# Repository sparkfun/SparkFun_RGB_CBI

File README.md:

SparkFun RGB Addressable CBI LED 5mm - Right Angle
========================================

[*SparkFun RGB Addressable CBI LED 5mm - Right Angle (COM-23649)*](https://www.sparkfun.com/products/23649)

This is a right angle 5mm addressable LED. It sounds boring, but at the time of writing, *this is the first one in the world*.

If you've ever tried to get a project into an enclosure, you know what a challenge it can be. Connectors are fairly straightforward. Oddly, getting a clean-looking, clear indicator to the outside world is trickier.

CBIs, or circuit board indicators, are a common way to get LEDs through the enclosure wall. The problem is that all the current LED suppliers and CBI models are from the 1980s when Modems were the king and needed lots of link indicators. When we wanted an addressable RGB CBI for our projects and couldn't find one, so we made it!

Inside is a single wire APA106/WS2812/Neopixel type RGB addressable LED with data in, and data out pins. Using the [FastLED library](https://fastled.io/), you'll be blinking in no time!

Why be locked into a single indicator LED color when you can drive *many* board edge indicators with a single wire, and make them any color or brightness! Welcome to the future.

Repository Contents
-------------------

* **/Documentation** - Dimensional drawing and LED information
* **/Firmware** - Example sketch showing how to drive with the FastLED library.
* **/Hardware** - Example PCB including footprint in KiCad.

License Information
-------------------

This product is _**open source**_! 

Please review the LICENSE.md file for license information. 

If you have any questions or concerns on licensing, please contact technical support on our [SparkFun forums](https://forum.sparkfun.com/viewforum.php?f=152).

Distributed as-is; no warranty is given.

- Your friends at SparkFun.

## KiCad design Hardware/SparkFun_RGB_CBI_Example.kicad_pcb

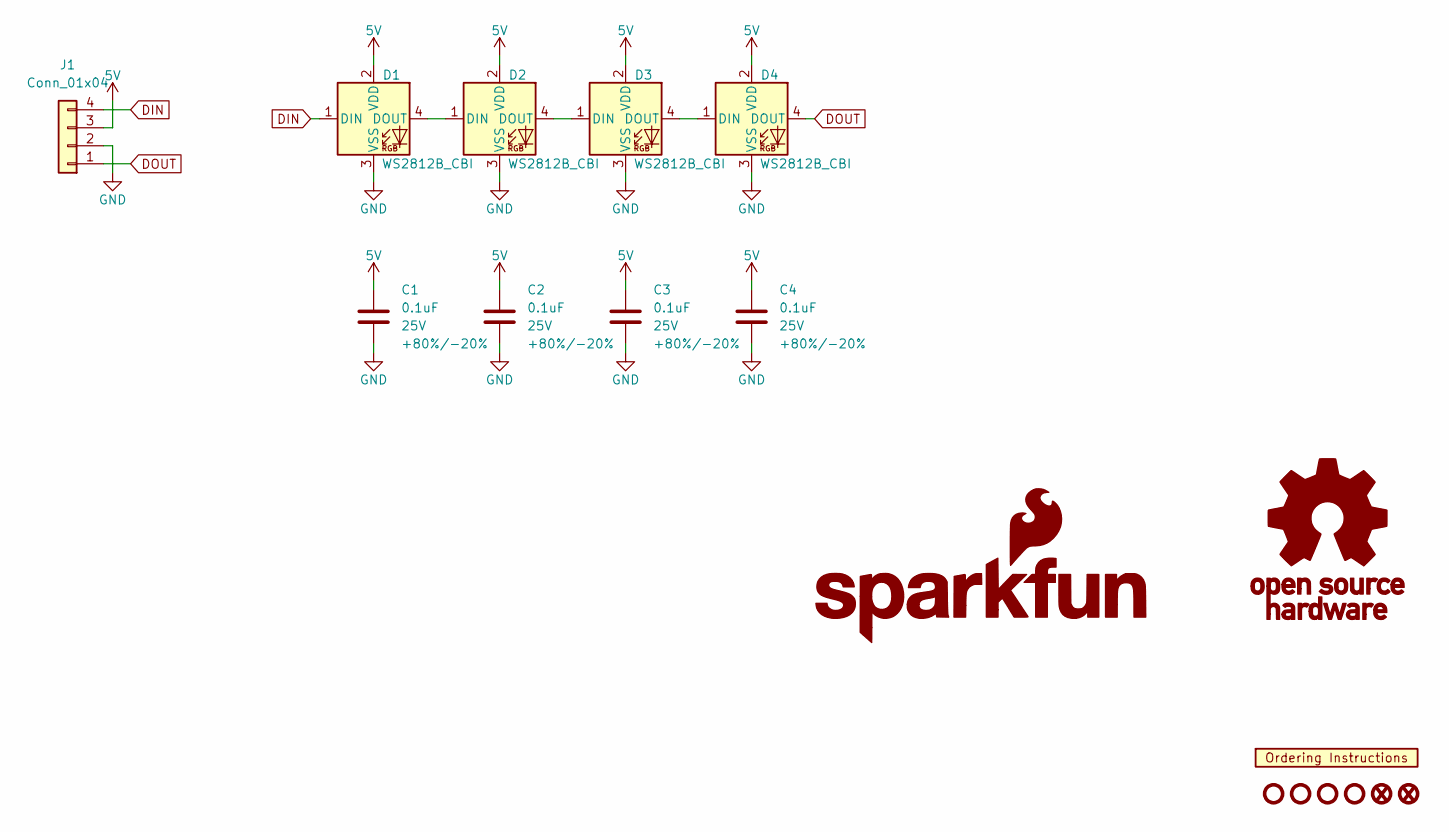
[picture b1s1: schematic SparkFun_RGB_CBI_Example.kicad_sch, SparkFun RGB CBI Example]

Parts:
C1, C2, C3, C4: 0.1uF; C_0603_1608Metric; Voltage 25V; Tolerance +80%/-20%
D1, D2, D3, D4: WS2812B_CBI; WS2812B-CBI_Datasheet
FID1, FID2: Fiducial_0.5mm; Fiducial_0.5mm_Mask1mm
G1: SparkFun_Logo
G2: OSHW_Logo; Creative_Commons_License
J1: Conn_01x04; 1X04
ST1, ST2, ST3, ST4: Stand_off; STAND-OFF
U1: ORDERING_INSTRUCTIONS

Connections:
5V: C1.1, C2.1, C3.1, C4.1, D1.2 (VDD), D2.2 (VDD), D3.2 (VDD), D4.2 (VDD), J1.3
DIN: D1.1 (DIN), J1.4
DOUT: D4.4 (DOUT), J1.1
GND: C1.2, C2.2, C3.2, C4.2, D1.3 (VSS), D2.3 (VSS), D3.3 (VSS), D4.3 (VSS), J1.2
unnamed: D1.4 (DOUT), D2.1 (DIN)
unnamed: D2.4 (DOUT), D3.1 (DIN)
unnamed: D3.4 (DOUT), D4.1 (DIN)

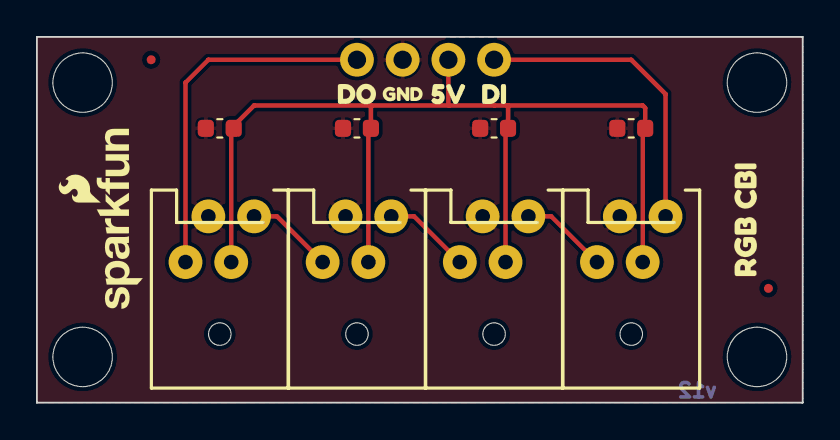
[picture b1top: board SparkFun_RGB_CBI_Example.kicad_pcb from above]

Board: 2 copper layers, 42.5 x 20.3 mm, 23 parts (1 on the bottom side), 7 nets.

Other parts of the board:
Ref**: Val**; OSHW_Logo_2.5mm
kibuzzard-6570C3FB: G***; kibuzzard-6570C3FB
kibuzzard-6570C40C: G***; kibuzzard-6570C40C
kibuzzard-6570C42B: G***; kibuzzard-6570C42B
kibuzzard-6570C414: G***; kibuzzard-6570C414
kibuzzard-6570C446: G***; kibuzzard-6570C446

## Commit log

2023-12-29 Add readme and license.
2024-01-04 Rename drawing file

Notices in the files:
parts and their libraries:
https://creativecommons.org/licenses/by-sa/4.0
Released under the Creative Commons Attribution Share-Alike 4.0 License
